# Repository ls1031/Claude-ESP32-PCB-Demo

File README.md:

# Claude-ESP32-PCB-Demo

A small demo board built around an **ESP32-S3-WROOM-1** module, powered and
programmed over **USB-C** (native USB, no USB-UART bridge). Designed in KiCad 10.

| Top | Bottom |
|---|---|
|  |  |

Schematic: [hardware/docs/schematic.pdf](hardware/docs/schematic.pdf)

## Board

- 36 × 46.5 mm, 2 layers, GND pour on both sides; antenna overhangs a copper-free zone at the top edge
- USB-C receptacle (GCT USB4105), 5.1 kΩ CC pull-downs (sink, 5 V default)
- USBLC6-2SC6 ESD on D+/D−, routed through the ESP32-S3 native USB (GPIO19/20)
- 500 mA polyfuse → AMS1117-3.3 LDO, 10 µF in/out, 22 µF + 100 nF at the module
- RESET (EN, with 10 k / 1 µF RC) and BOOT (GPIO0) tact switches, power LED
- J2 (1×8): 3V3, GND, IO4, IO5, IO6, IO7, IO15, IO16
- J3 (1×5): IO1, IO2, TXD0, RXD0, GND

## Files

```
hardware/
  esp32s3-usbc/   KiCad project (.kicad_pro / .kicad_sch / .kicad_pcb)
  scripts/        generators that produce the schematic and board
  docs/           renders and schematic PDF
```

The schematic and layout are generated from `hardware/scripts/design.py`
(parts, footprints, nets, placement). To rebuild after editing it:

```bash
cd hardware/scripts
"C:/Program Files/KiCad/10.0/bin/python.exe" gen_schematic.py
"C:/Program Files/KiCad/10.0/bin/python.exe" gen_pcb.py
```

`gen_pcb.py` uses KiCad's bundled Python (`pcbnew`); routes are listed in its
`ROUTES` table. Regenerating overwrites the `.kicad_sch` / `.kicad_pcb`, so if
you start editing by hand in KiCad, stop using the scripts.

## Checks

- ERC: 0 violations
- DRC (with schematic parity): 0 errors, 0 unconnected. Remaining warnings are
  one silkscreen-over-pad nit and `ki_fp_filters` field-mismatch notices.

This is a quick demo, not a production-reviewed design: the USB pair is
short and length-matched but not impedance-controlled (fine for 12 Mbit/s
full-speed), and the AMS1117 has a high dropout, so 3V3 sags if VBUS drops
much below 4.5 V.

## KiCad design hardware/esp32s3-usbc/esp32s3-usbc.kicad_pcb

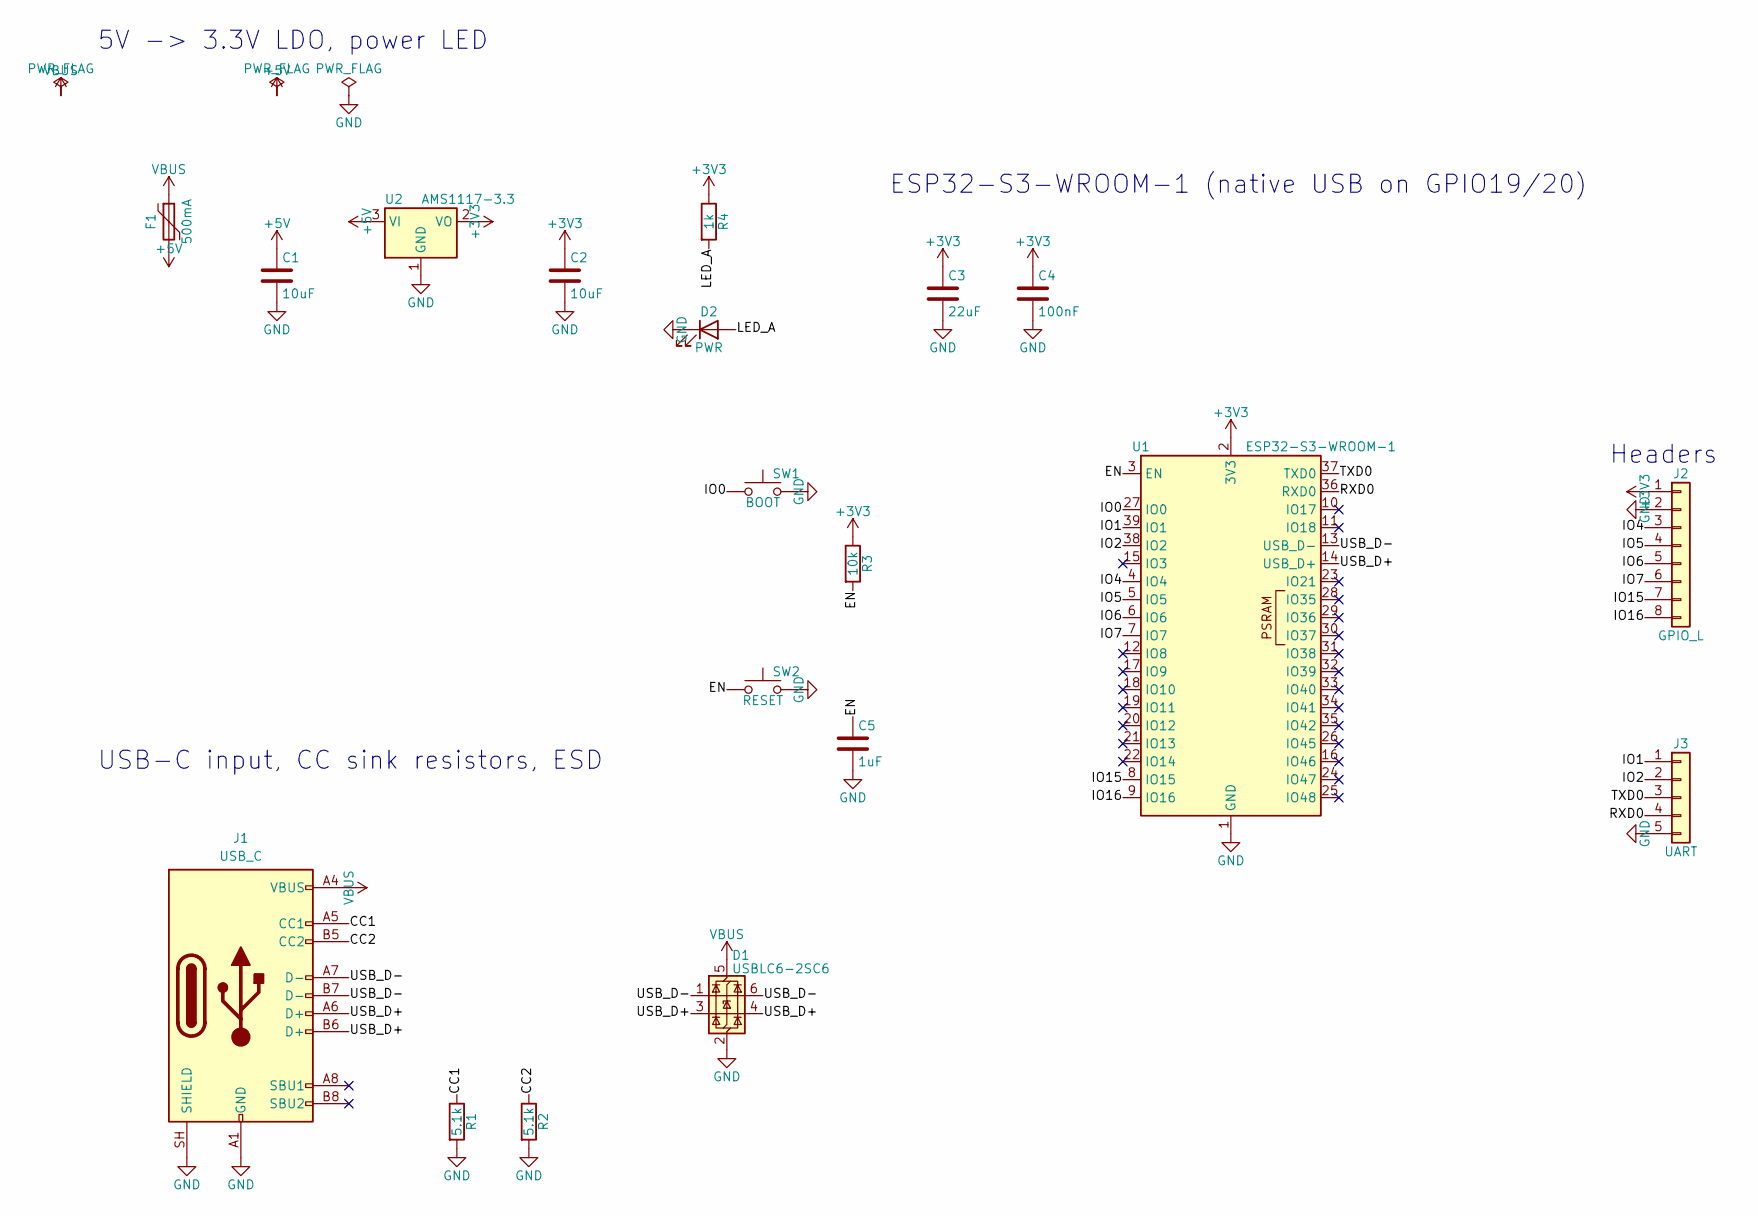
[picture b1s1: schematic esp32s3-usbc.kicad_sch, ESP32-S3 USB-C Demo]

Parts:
C1, C2: 10uF; C_0805_2012Metric
C3: 22uF; C_0805_2012Metric
C4: 100nF; C_0402_1005Metric
C5: 1uF; C_0603_1608Metric
D1: USBLC6-2SC6; SOT-23-6
D2: PWR; LED_0603_1608Metric
F1: 500mA; Fuse_1206_3216Metric
J1: USB_C; USB_C_Receptacle_GCT_USB4105-xx-A_16P_TopMnt_Horizontal
J2: GPIO_L; PinHeader_1x08_P2.54mm_Vertical
J3: UART; PinHeader_1x05_P2.54mm_Vertical
R1, R2: 5.1k; R_0603_1608Metric
R3: 10k; R_0603_1608Metric
R4: 1k; R_0603_1608Metric
SW1: BOOT; SW_SPST_PTS645Sx43SMTR92
SW2: RESET; SW_SPST_PTS645Sx43SMTR92
U1: ESP32-S3-WROOM-1
U2: AMS1117-3.3; SOT-223-3_TabPin2

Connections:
+3V3: C2.1, C3.1, C4.1, J2.1, R3.1, R4.1, U1.2 (3V3), U2.2 (VO)
+5V: C1.1, F1.2, U2.3 (VI)
/CC1: J1.A5 (CC1), R1.1
/CC2: J1.B5 (CC2), R2.1
/EN: C5.1, R3.2, SW2.1, U1.3 (EN)
/IO0: SW1.1, U1.27 (IO0)
/IO1: J3.1, U1.39 (IO1)
/IO2: J3.2, U1.38 (IO2)
/IO4: J2.3, U1.4 (IO4)
/IO5: J2.4, U1.5 (IO5)
/IO6: J2.5, U1.6 (IO6)
/IO7: J2.6, U1.7 (IO7)
/IO15: J2.7, U1.8 (IO15)
/IO16: J2.8, U1.9 (IO16)
/LED_A: D2.2 (A), R4.2
/RXD0: J3.4, U1.36 (RXD0)
/TXD0: J3.3, U1.37 (TXD0)
/USB_D+: D1.3 (I/O2), D1.4 (I/O2), J1.A6 (D+), J1.B6 (D+), U1.14 (USB_D+)
/USB_D-: D1.1 (I/O1), D1.6 (I/O1), J1.A7 (D-), J1.B7 (D-), U1.13 (USB_D-)
GND: C1.2, C2.2, C3.2, C4.2, C5.2, D1.2 (GND), D2.1 (K), J1.A1 (GND), J1.A12 (GND), J1.B1 (GND), J1.B12 (GND), J1.SH (SHIELD), J2.2, J3.5, R1.2, R2.2, SW1.2, SW2.2, U1.1 (GND), U1.40 (GND), U1.41 (GND), U2.1 (GND)
VBUS: D1.5 (VBUS), F1.1, J1.A4 (VBUS), J1.A9 (VBUS), J1.B4 (VBUS), J1.B9 (VBUS)

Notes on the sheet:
USB-C input, CC sink resistors, ESD
5V -> 3.3V LDO, power LED
ESP32-S3-WROOM-1 (native USB on GPIO19/20)
Headers

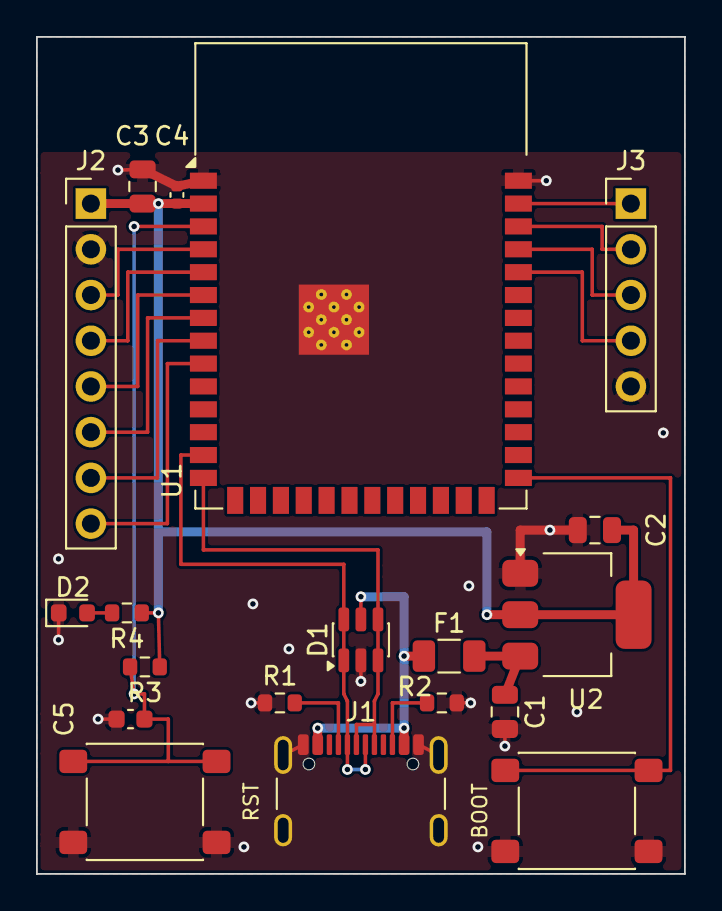
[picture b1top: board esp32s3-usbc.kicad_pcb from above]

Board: 2 copper layers, 36.0 x 46.5 mm, 19 parts (0 on the bottom side), 21 nets.
